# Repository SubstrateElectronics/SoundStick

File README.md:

# SoundStick
An eraser sized music player/walkie-talkie supporting Bluetooth and SD card playback.

> [!NOTE]
> ## License
> The **Hardware Design Files (`.kicad_sch`, `.kicad_pcb`, schematics, gerbers):** are Licensed under the [**CERN Open Hardware Licence v2 (Weakly Reciprocal) - CERN-OHL-W**](https://gitlab.com/ohwr/project/cernohl/-/wikis/Documents/CERN-OHL-version-2). You are free to use, study, and privately modify the hardware. However, if you publicly distribute or mass-produce modified versions of these board designs, you must open-source your modified hardware design files under the same license terms. See the [LICENSE](LICENSE) file for details.

> [!WARNING]
> Use at your own risk. Hasn't been tested yet.

## Components
- nRF52840 QFN48 Variant
- MCP73831 Li-ion Charger
- XC6206 3.3v LDO
- MAX98357A I2C AMP
- MP34DT05 MEMS Microphone
- DM3AT MicroSD Slot
- USB-C 6P

## Features
- SD Card & Bluetooth audio playback
- 4 configurable buttons
- Onboard Li-ion battery charger
- Low Power Consumption
- SSD1306 OLED display support

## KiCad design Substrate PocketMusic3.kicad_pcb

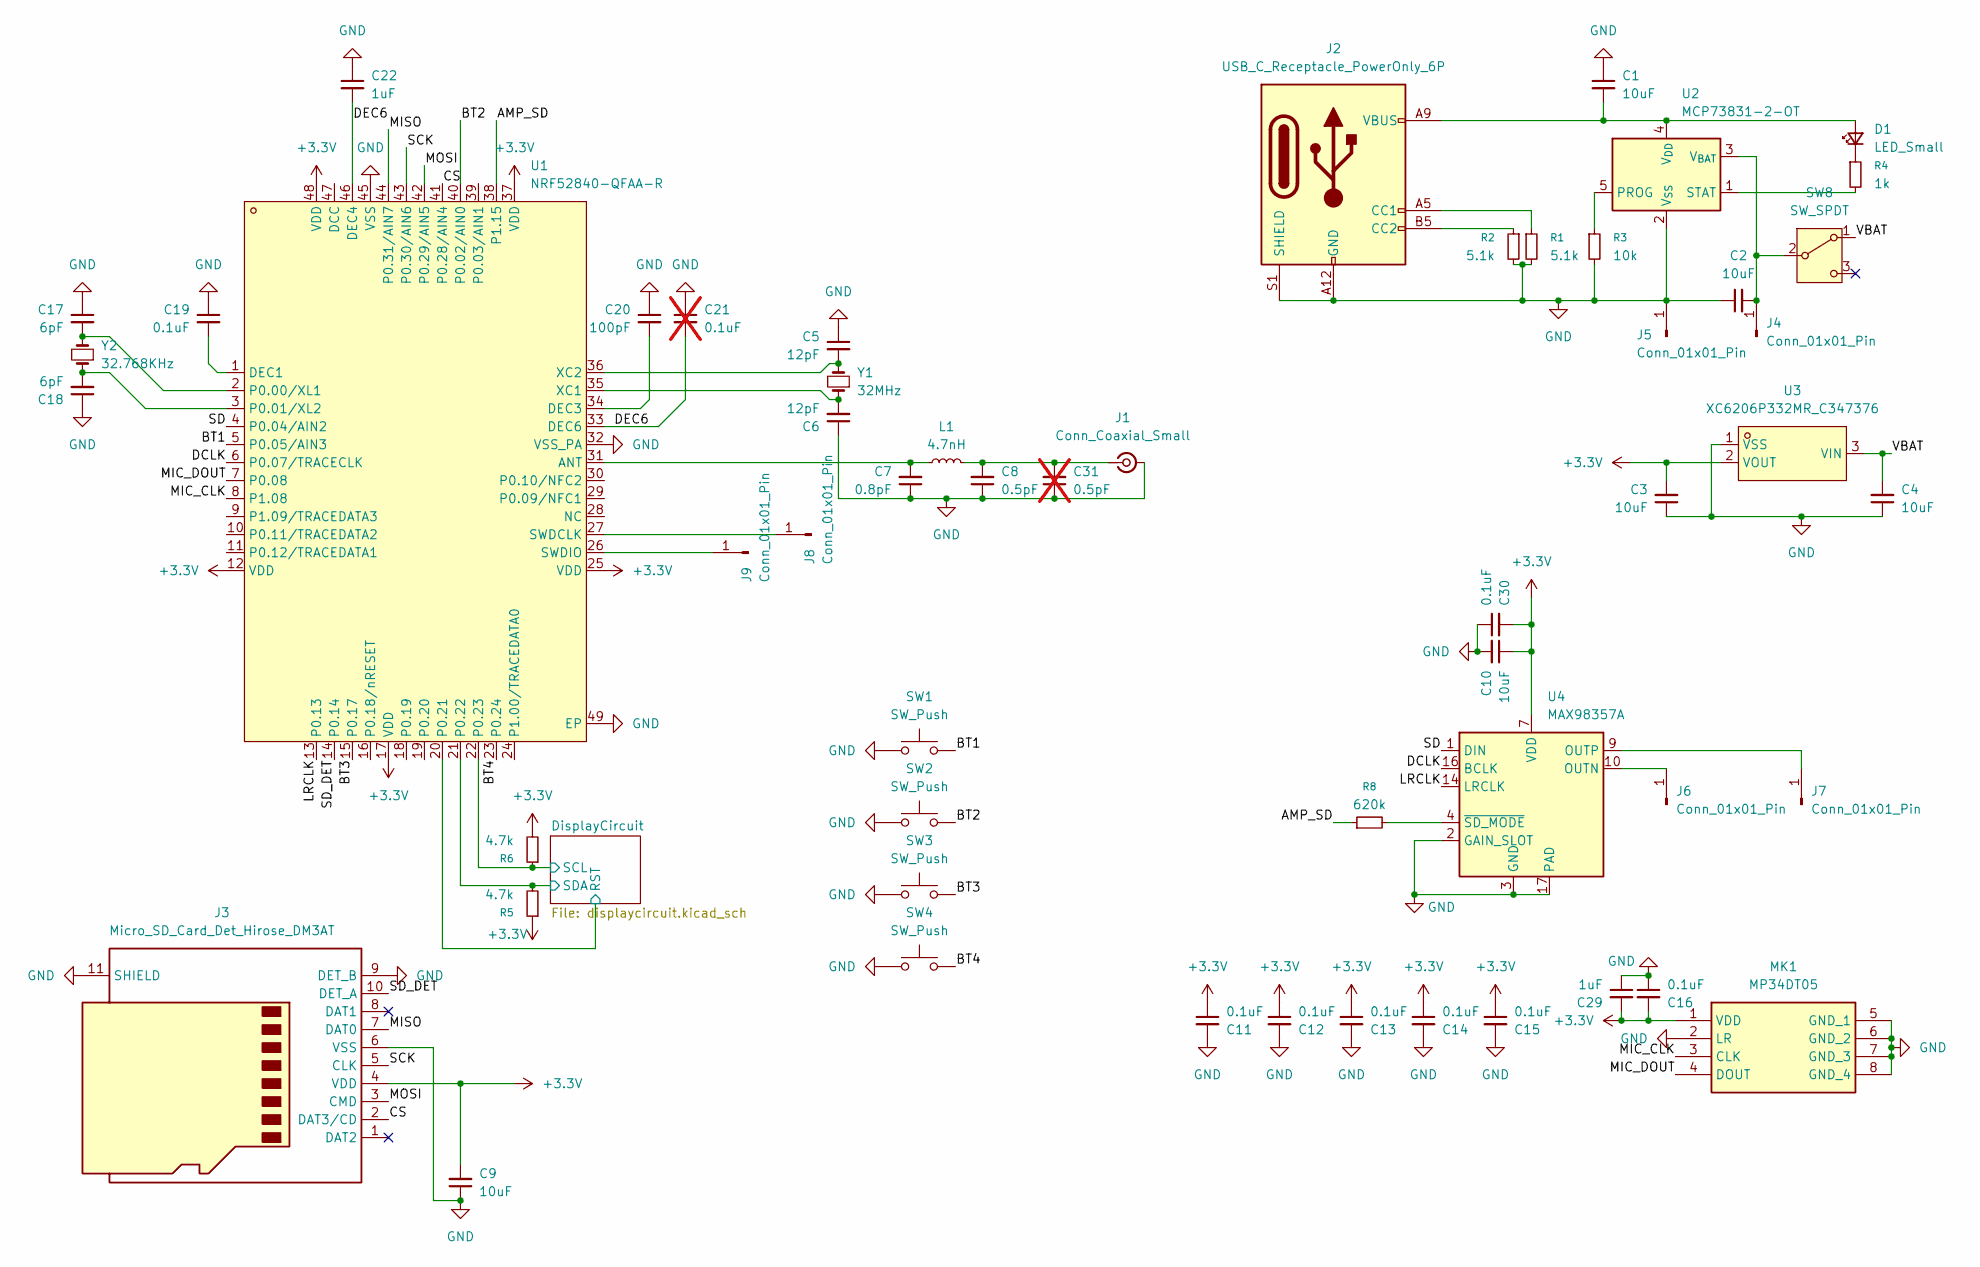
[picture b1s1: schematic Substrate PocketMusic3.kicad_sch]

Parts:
C1, C2, C3, C4, C9, C10: 10uF; C_0603_1608Metric
C5, C6: 12pF; C_0603_1608Metric
C7: 0.8pF; C_0402_1005Metric
C8: 0.5pF; C_0402_1005Metric
C11, C12, C13, C14, C15, C16, C30: 0.1uF; C_0402_1005Metric
C17, C18: 6pF; C_0603_1608Metric
C19: 0.1uF; C_0603_1608Metric
C20: 100pF; C_0402_1005Metric
C21: 0.1uF; C_0402_1005Metric; not fitted
C22: 1uF; C_0603_1608Metric
C29: 1uF; C_0402_1005Metric
C31: 0.5pF; C_0402_1005Metric; not fitted
D1: LED_Small; LED_0603_1608Metric
J1: Conn_Coaxial_Small; U.FL_Hirose_U.FL-R-SMT-1_Vertical
J2: USB_C_Receptacle_PowerOnly_6P; USB_C_Receptacle_GCT_USB4125-xx-x_6P_TopMnt_Horizontal
J3: Micro_SD_Card_Det_Hirose_DM3AT; microSD_HC_Hirose_DM3AT-SF-PEJM5
J4, J5, J6, J7, J8, J9: Conn_01x01_Pin; TestPoint_Pad_D3.0mm
L1: 4.7nH; L_0402_1005Metric
MK1: MP34DT05; Manufacturer_Part_Number MP34DT05; Mouser Part Number N/A
R1, R2: 5.1k; R_0402_1005Metric
R3: 10k; R_0603_1608Metric
R4: 1k; R_0402_1005Metric
R5, R6: 4.7k; R_0402_1005Metric
R8: 620k; R_0603_1608Metric
SW1, SW2, SW3, SW4: SW_Push; SW-SMD_HX-3X6X3.5-CA-0.6-2.5N
SW8: SW_SPDT; SW_SPDT_Shouhan_MSK12C02
U1: NRF52840-QFAA-R; QFN-48_L6.0-W6.0-P0.40-TL-EP4.6; MPN NRF52840-QFAA-R; LCSC Part C3606885
U2: MCP73831-2-OT; SOT-23-5
U3: XC6206P332MR_C347376; SOT-23-3; MPN XC6206P332MR; LCSC Part C347376
U4: MAX98357A; TQFN-16-1EP_3x3mm_P0.5mm_EP1.23x1.23mm
Y1: 32MHz; Crystal_SMD_3225-4Pin_3.2x2.5mm
Y2: 32.768KHz; Crystal_SMD_3215-2Pin_3.2x1.5mm

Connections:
+3.3V: C3.2, C9.2, C10.1, C11.1, C12.1, C13.1, C14.1, C15.1, C16.2, C29.2, C30.2, J3.4 (VDD), MK1.1 (VDD), R5.1, R6.2, U1.12 (VDD), U1.17 (VDD), U1.25 (VDD), U1.37 (VDD), U1.48 (VDD), U3.2 (VOUT), U4.7 (VDD), U4.8 (VDD); also elsewhere on the board
/AMP_SD: R8.1, U1.38 (P1.15)
/BT1: SW1.2, U1.5 (P0.05/AIN3)
/BT2: SW2.2, U1.40 (P0.02/AIN0)
/BT3: SW3.2, U1.15 (P0.17)
/BT4: SW4.2, U1.23 (P0.24)
/CS: J3.2 (DAT3/CD), U1.41 (P0.28/AIN4)
/DCLK: U1.6 (P0.07/TRACECLK), U4.16 (BCLK)
/DEC6: C21.2, C22.2, U1.33 (DEC6), U1.46 (DEC4)
/DisplayCircuit/RST: U1.20 (P0.21); also elsewhere on the board
/DisplayCircuit/SCL: R6.1, U1.22 (P0.23); also elsewhere on the board
/DisplayCircuit/SDA: R5.2, U1.21 (P0.22); also elsewhere on the board
/LRCLK: U1.13 (P0.13), U4.14 (LRCLK)
/MIC_CLK: MK1.3 (CLK), U1.8 (P1.08)
/MIC_DOUT: MK1.4 (DOUT), U1.7 (P0.08)
/MISO: J3.7 (DAT0), U1.44 (P0.31/AIN7)
/MOSI: J3.3 (CMD), U1.42 (P0.29/AIN5)
/SCK: J3.5 (CLK), U1.43 (P0.30/AIN6)
/SD: U1.4 (P0.04/AIN2), U4.1 (DIN)
/SD_DET: J3.10 (DET_A), U1.14 (P0.14)
/VBAT: C4.2, SW8.1 (A), U3.3 (VIN)
GND: C1.1, C2.1, C3.1, C4.1, C5.1, C6.1, C7.1, C8.1, C9.1, C10.2, C11.2, C12.2, C13.2, C14.2, C15.2, C16.1, C17.1, C18.1, C19.1, C20.1, C21.1, C22.1, C29.1, C30.1, C31.1, J1.2 (Ext), J2.A12 (GND), J2.B12 (GND), J2.S1 (SHIELD), J3.6 (VSS), J3.9 (DET_B), J3.11 (SHIELD), J5.1 (Pin_1_1), MK1.2 (LR), MK1.5 (GND_1), MK1.6 (GND_2), MK1.7 (GND_3), MK1.8 (GND_4), R1.2, R2.2, R3.2, SW1.1, SW2.1, SW3.1, SW4.1, U1.32 (VSS_PA), U1.45 (VSS), U1.49 (EP), U2.2 (V_{SS}), U3.1 (VSS), U4.2 (GAIN_SLOT), U4.3 (GND), U4.11 (GND), U4.15 (GND), U4.17 (PAD); also elsewhere on the board
unnamed: C1.2, D1.2 (A), J2.A9 (VBUS), J2.B9 (VBUS), U2.4 (V_{DD})
unnamed: D1.1 (K), R4.1
unnamed: C8.2, C31.2, J1.1 (In), L1.2
unnamed: J2.A5 (CC1), R1.1
unnamed: J2.B5 (CC2), R2.1
unnamed: C2.2, J4.1 (Pin_1_1), SW8.2 (B), U2.3 (V_{BAT})
unnamed: J6.1 (Pin_1_1), U4.10 (OUTN)
unnamed: J7.1 (Pin_1_1), U4.9 (OUTP)
unnamed: J8.1 (Pin_1_1), U1.27 (SWDCLK)
unnamed: J9.1 (Pin_1_1), U1.26 (SWDIO)
unnamed: C7.2, L1.1, U1.31 (ANT)
unnamed: C19.2, U1.1 (DEC1)
unnamed: C20.2, U1.34 (DEC3)
unnamed: C17.2, U1.2 (P0.00/XL1), Y2.2
unnamed: C18.2, U1.3 (P0.01/XL2), Y2.1
unnamed: C6.2, U1.35 (XC1), Y1.1
unnamed: C5.2, U1.36 (XC2), Y1.2
unnamed: R3.1, U2.5 (PROG)
unnamed: R4.2, U2.1 (STAT)
unnamed: R8.2, U4.4 (~SD_MODE)

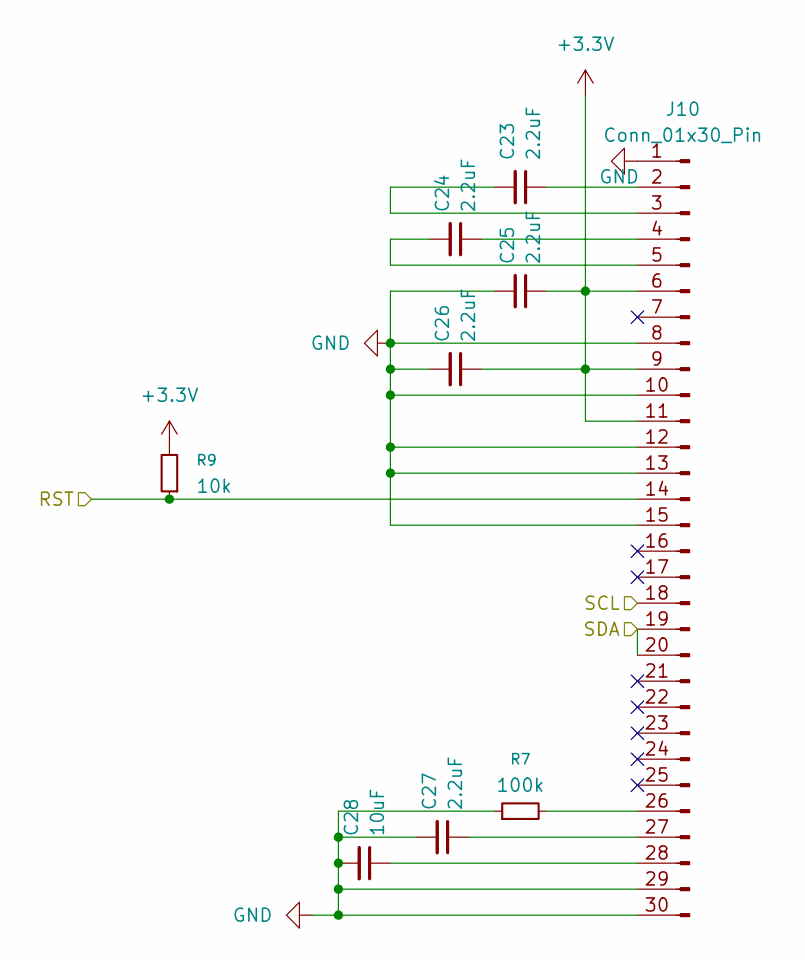
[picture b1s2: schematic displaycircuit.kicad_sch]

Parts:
C23, C24, C25, C26, C27: 2.2uF; C_0402_1005Metric
C28: 10uF; C_0603_1608Metric
J10: Conn_01x30_Pin; 30P_0.7mm
R7: 100k; R_0402_1005Metric
R9: 10k; R_0402_1005Metric

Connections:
+3.3V: C25.1, C26.1, J10.6, J10.9, J10.11, R9.2; also elsewhere on the board
/DisplayCircuit/RST: J10.14, R9.1; also elsewhere on the board
/DisplayCircuit/SCL: J10.18; also elsewhere on the board
/DisplayCircuit/SDA: J10.19, J10.20; also elsewhere on the board
GND: C25.2, C26.2, C27.2, C28.2, J10.1, J10.8, J10.10, J10.12, J10.13, J10.15, J10.29, J10.30, R7.1; also elsewhere on the board
unnamed: C23.1, J10.2
unnamed: C23.2, J10.3
unnamed: C24.1, J10.4
unnamed: C24.2, J10.5
unnamed: J10.26, R7.2
unnamed: C27.1, J10.27
unnamed: C28.1, J10.28

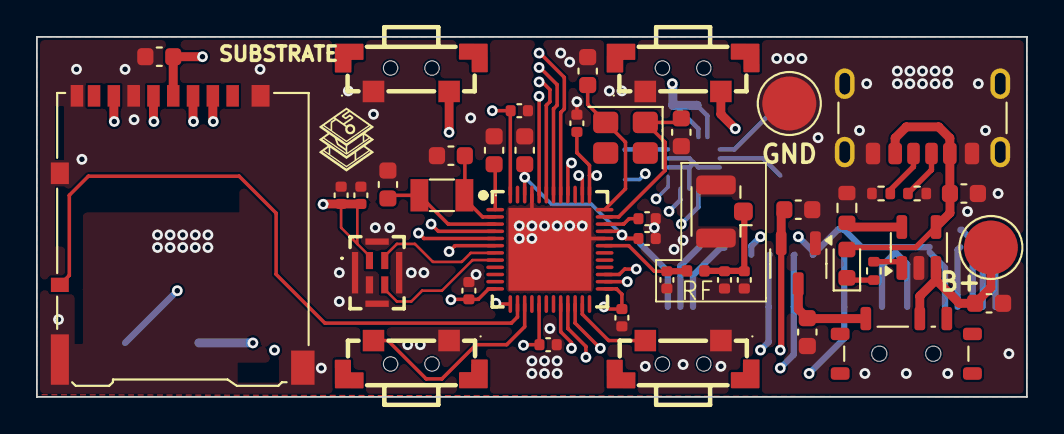
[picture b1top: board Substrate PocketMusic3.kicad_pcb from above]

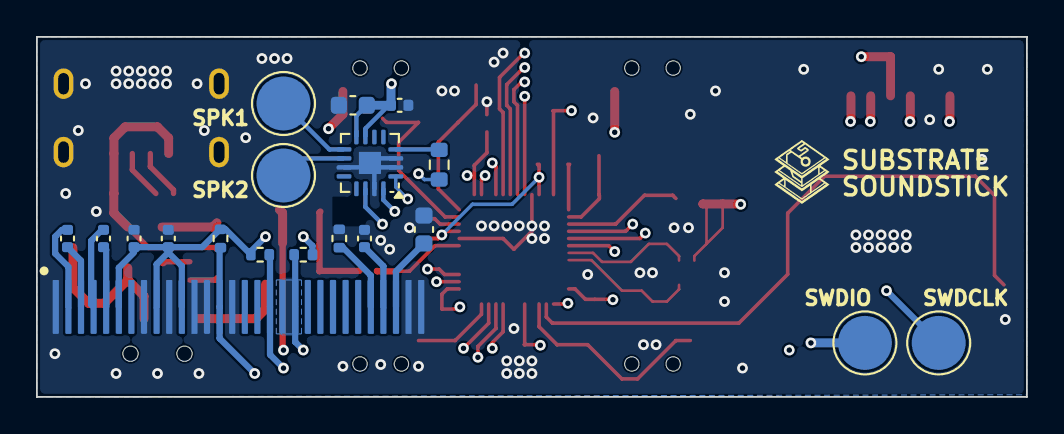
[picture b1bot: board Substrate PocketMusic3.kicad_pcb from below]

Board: 4 copper layers, 55.0 x 20.0 mm, 64 parts (19 on the bottom side), 49 nets.

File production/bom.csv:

Designator,Footprint,Quantity,Value,LCSC Part #
"C1, C10, C2, C28, C3, C4, C9",0603,7,10uF,
"C11, C12, C13, C14, C15, C16, C21, C30",0402,8,0.1uF,
"C17, C18",0603,2,6pF,
C19,0603,1,0.1uF,
C20,0402,1,100pF,
C22,0603,1,1uF,
"C23, C24, C25, C26, C27",0402,5,2.2uF,
C29,0402,1,1uF,
"C31, C8",0402,2,0.5pF,
"C5, C6",0603,2,12pF,
C7,0402,1,0.8pF,
D1,0603,1,LED_Small,
J1,U.FL_Hirose_U.FL-R-SMT-1_Vertical,1,Conn_Coaxial_Small,
J10,30P_0.7mm,1,Conn_01x30_Pin,
J2,USB_C_Receptacle_GCT_USB4125-xx-x_6P_TopMnt_Horizontal,1,USB_C_Receptacle_PowerOnly_6P,
J3,microSD_HC_Hirose_DM3AT-SF-PEJM5,1,Micro_SD_Card_Det_Hirose_DM3AT,
"J4, J5, J6, J7, J8, J9",TestPoint_Pad_D3.0mm,6,Conn_01x01_Pin,
L1,0402,1,4.7nH,
MK1,MP34DT05,1,MP34DT05,
"R1, R2",0402,2,5.1k,
R3,0603,1,10k,
R4,0402,1,1k,
"R5, R6",0402,2,4.7k,
R7,0402,1,100k,
R8,0603,1,620k,
R9,0402,1,10k,
"SW1, SW2, SW3, SW4",SW-SMD_HX-3X6X3.5-CA-0.6-2.5N,4,SW_Push,C49234146
SW8,SW_SPDT_Shouhan_MSK12C02,1,SW_SPDT,
U1,QFN-48_L6.0-W6.0-P0.40-TL-EP4.6,1,NRF52840-QFAA-R,C3606885
U2,SOT-23-5,1,MCP73831-2-OT,
U3,SOT-23-3,1,XC6206P332MR_C347376,
U4,TQFN-16-1EP_3x3mm_P0.5mm_EP1.23x1.23mm,1,MAX98357A,
Y1,Crystal_SMD_3225-4Pin_3.2x2.5mm,1,32MHz,
Y2,Crystal_SMD_3215-2Pin_3.2x1.5mm,1,32.768KHz,
